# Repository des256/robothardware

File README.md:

# robothardware — Robot Backbone PCB

KiCad workspace for the backbone board described in [`HARDWARE.md`](HARDWARE.md)
(how and with what) and [`FUNCTIONAL.md`](FUNCTIONAL.md) (what it does, seen from
its connectors and from software).
Tooling follows [kevins-kicad-helpers](https://github.com/lynaghk/kevins-kicad-helpers)
(vendored at `vendor/kevins-kicad-helpers`, on PATH via `mise.toml`).

## Toolchain status

1. **mise** — installed at `~/.local/bin/mise`; activate in your shell
   (`eval "$(mise activate bash)"` in `~/.bashrc`, the installer appended it).
   Run `mise trust && mise install` once in this directory.
2. **sqlite3** — static binary at `~/.local/bin/sqlite3` (needed by the
   parts-database script; not in mise).
3. **KiCad 10** — installed (10.0.6; verify with `kicad-cli --version`).
4. **KiCad plugins** — installed: bennymeg/Fabrication-Toolkit (JLCPCB outputs;
   `kkh build` drives it) and CDFER/JLCPCB-Kicad-Library (symbols/footprints
   for JLC Basic parts).
5. **Analyzer toolchain** (`kkh check` / `kkh-analyze-schematic` run a JVM
   Clojure tool) — Java temurin-25 and clj-kondo via
   `mise -C vendor/kevins-kicad-helpers/analyzer install`. Clojure needs a
   workaround: mise 2026.8.14 cannot resolve the registry name `clojure`, so
   the CLI was installed through the asdf plugin the analyzer's `mise.lock`
   names (`mise plugins install clojure https://github.com/asdf-community/asdf-clojure.git`)
   and symlinked onto the PATH: `~/.local/bin/{clojure,clj}` →
   `~/.local/share/mise/installs/clojure/1.12.5.1654/bin/`. `mise exec` then
   finds it from the ambient PATH. Verified: `kkh-analyze-schematic` runs.
6. **`KICAD_PYTHON`** — set in `mise.toml` to `/usr/bin/python3` (the PATH
   `python3` is PlatformIO's venv and cannot import `pcbnew`).

## Project layout

- `backbone/` — the KiCad project (`backbone.kicad_pro`, root sheet plus one file
  per block, see below); kkh tools discover it by scanning for `*.kicad_pro`.
  `0_backbone.kicad_sym` / `0_backbone.pretty/` / `0_backbone.3dshapes/` are the
  project-local libraries written by `kkh-import-easyeda-parts` (registered in
  the project `sym-lib-table` / `fp-lib-table`; reopen the project in KiCad
  after an import so it picks them up). Library status is tracked in the
  Schematic plan section.
- `jlcpcb_parts.db` — local JLCPCB catalog mirror (gitignored; rebuild anytime
  with `kkh-download-jlcpcb-parts-database jlcpcb_parts.db`). Check freshness:
  `sqlite3 jlcpcb_parts.db "SELECT value FROM meta WHERE key='generated_at'"`.
- `parts-shortlist.md` — distilled candidate parts per block, queried from the DB.
- `datasheets/` — part datasheets for every curated pick plus vendor reference
  designs and the ROBOTIS servo circuits (`datasheets/README.md` is the index;
  `datasheets/fetch.sh` re-downloads from `manifest.tsv`).

## Schematic plan (mirrors HARDWARE.md sections 1 and 8)

The hierarchy lives in `backbone/`. The root sheet `backbone.kicad_sch` is the
block diagram of FUNCTIONAL.md §3 and holds only sheet symbols; every block is
its own file, and the two repeated blocks are one file instantiated several
times:

| Page | Sheet file | Instances | Contents | Golden reference |
|------|------------|-----------|----------|------------------|
| 2 | `input` | 1 | J1, fuse, LM74700 + FET, SMBJ24A, bulk; J2 19 V out with its fuse | LM74700 datasheet |
| 3 | `buck-12v-servo` | 1 | LM5145 → `+12V_SERVO`, shared bulk bank | LM5145 EVM / WEBENCH |
| 4 | `buck-5v-servo` | 1 | LM5145 → `+5V_SERVO` (own file: values differ, and D1 may delete it) | same |
| 5 | `buck-5v-usb` | 1 | TPS54560 → `+5V_USB`, TLV62569 → `+3V3` | TPS54560 EVM |
| 6 | `usbc-upstream` | 1 | J3, HD3SS3220 (UFP, GPIO mode), VBUS_DET, ESD | HD3SS3220 checklist + EVM |
| 7 | `usb-hub` | 1 | TUSB8041, crystal, 1V1 LDO, straps, USB_VBUS divider | TUSB8041 EVM |
| 8–10 | `usb-port` | 3: `usb-port-1..3` = hub DS1..DS3 | SY6280 + Rset, TPD4E05U06, USBLC6-2, USB-A 3.0 receptacle | hub EVM downstream port |
| 11 | `servo-uart` | 1 | CH344Q on hub DS4, TNOW pull-downs, RXD pull-ups | CH344 datasheet |
| 12–15 | `servo-port` | 4: `servo-port-0..3` = CH344 UART0..3 | SP3485EN + LVC2G241 front-end, mode jumper, ESD, both connectors, both e-fuses / bulk / TVS | ROBOTIS circuits |

Every sheet starts with a note (golden references, LCSC parts, rails, open
FUNCTIONAL.md decisions) and its hierarchical pins on wire stubs. Anything that
must differ between instances cannot live in a multi-instance sheet: KiCad
stores only reference and unit per instance; values, footprints and DNP are
shared.

Conventions (see HARDWARE.md section 8):

- Rails are global power symbols — `+19V_IN`, `+19V_JETSON`, `+12V_SERVO`,
  `+5V_SERVO`, `+5V_USB`, `+3V3`, `+1V1_HUB`, `VBUS`, `GND` — with the
  `PWR_FLAG` on the sheet that produces the rail. In KiCad 10 a power symbol's
  Value is its net name, so a `power:+5V` symbol with Value `+5V_SERVO` *is*
  the `+5V_SERVO` rail. `VBUS` is reserved for the upstream USB-C VBUS (the
  < 10 µF check); the switched port outputs are `VBUS_OUT`.
- Signals cross sheets through hierarchical pins; the labels on the root name
  the top-level nets (`US_*` upstream ↔ hub, `DSn_*` hub ↔ ports, `UARTn_*`
  uart ↔ servo ports). Inside a multi-instance sheet nets get paths such as
  `/servo-port-0/DATA` — the net-class patterns and DRC rules key on them.
- Annotate with "First free after sheet number × 100" so a designator names
  its sheet; the pre-placed power symbols already follow it (`#PWR0201` is on
  sheet 2). This will renumber FUNCTIONAL.md's J1–J14 — update that table once
  the connectors are placed.
- `max_mA`: `kkh-analyze-schematic` sums every `max_mA` in the design
  regardless of rail and asserts ≤ 300 mA (hardcoded in
  `vendor/kevins-kicad-helpers/analyzer/src/kicad_analyzer/core.clj`), so put
  it only on the +3V3 ICs. The rail budgets stay in FUNCTIONAL.md §4.
- `kkh check` fails any placed part (non-DNP, with a footprint) whose `LCSC`
  field is empty — CDFER-library and `kkh-import-easyeda-parts` symbols carry
  it, symbols taken from KiCad's own libraries (`Device:R`, …) need it filled
  in by hand.

### Library status (what `kkh-import-easyeda-parts` has pulled so far)

Imported into `0_backbone` from LCSC, with the EasyEDA footprint and 3D model
(non-interactive run, so no KiCad standard footprint was substituted — review
each footprint against the datasheet drawing, V4):
TUSB8041IRGCR, CH344Q, SN74LVC2G241DCU, LM5145RGYR, TPS54560DDAR,
TLV62569DBVR, TPS16630PWPR, TPS25961DRVR, SY6280AAC, HD3SS3220RNHR,
LM74700QDBVRQ1, TPD4E05U06DQAR, USBLC6-2SC6, B4B-EH-A, B3B-EH-A, XT30PW-M,
HC-ST-003-01-J (USB-A 3.0), TYPE-C 24P QT.

Served by the installed CDFER JLCPCB library instead (symbols already carry
the LCSC field; place them from `PCM_JLCPCB-…`): SP3485EN-L/TR, SMBJ24A,
SMBJ13A, SMBJ6.0A, SM712.

KiCad's own libraries also ship symbols for TUSB8041, CH344Q, TLV62569DBV,
LM74700, TPD4E05U06DQA and USBLC6-2SC6 — either is fine, but a symbol taken
from KiCad's library needs its `LCSC` field filled by hand.

Alternates, imported as well so a swap is a symbol change: RTS5411S-GR,
CYUSB3304-68LTXC, CH344L, SN74LVC1G126DBVR, SN74LVC1G125DBVR, LM5143RHAR,
TPS2553DBVR, S4B-EH, S3B-EH, DC-005-A200, TYPE-C 24P QCHT.

EasyEDA's API rate-limits bulk pulls (HTTP 403 after ~20 parts within a
minute); wait a few minutes and rerun the same command for the parts that
failed. Reruns skip parts the library already has.

### Schematic ↔ PCB correspondence

KiCad has no sheet-to-layer mapping; sheets are functional, layers are copper.
The links that do exist, and where each one is set up:

| Link | Where | State |
|------|-------|-------|
| Stackup | `backbone.kicad_pcb`: 4 copper layers, In1.Cu named `GND` (plane), In2.Cu named `PWR` | set; enter the JLC04161H-7628 thicknesses in Board Setup → Physical Stackup |
| Net classes | `backbone.kicad_pro`: `USB3_SS`, `USB2_HS`, `RS485`, `TTL_DATA`, `PWR_19V`, `PWR_SERVO`, `PWR_USB`, `SW_NODE` | defined; USB3_SS / USB2_HS width and gap **still to fill from the JLCPCB impedance calculator** (they inherit Default until then); power-class widths are starting values |
| Class of a signal net | directive label on its stub inside the sheet (a multi-instance sheet applies it to every instance) | placed on every USB pair |
| Class of a rail / per-port net | `netclass_patterns` in `backbone.kicad_pro`: `+12V_SERVO`, `/servo-port-*/A`, `/servo-port-*/B`, `/servo-port-*/DATA`, `/servo-port-*/VDD_*`, `/usb-port-*/VBUS_OUT`, `/buck-*/SW*`, `/buck-*/BOOT*` | set — use these net names when drawing |
| Layer geometry and keep-outs | `backbone.kicad_dru`: USB3_SS on F.Cu only and without vias, 1 mm zone clearance to the USB pairs, SW_NODE on outer layers and 3 mm from signal classes, PWR_SERVO copper barred from a rule area named `usb_section` (draw and name it in the PCB editor) | written; check it with Board Setup → Custom Rules → "Check rule syntax" — `kicad-cli pcb drc` silently ignores rule-file errors |
| Sheet → board region | PCB editor: "Generate Placement Rule Areas…" (one area per hierarchical sheet), then "Pack and Move Footprints" | use after the first Update PCB from Schematic |
| Sheet → component class | `sheet_component_classes` enabled in `backbone.kicad_pro`; rules can use `A.hasComponentClass(...)` | enabled |

Workflow while drawing sheets. ERC on the skeleton reports only "Label not
connected", "Unconnected wire endpoint" and "Pin not connected" — one per
interface pin or rail that has no part on it yet; they disappear as the sheets
fill up. `kkh check` therefore stops at ERC until then, and afterwards at the
DRC schematic-parity step until footprints are placed:

```sh
kicad-cli sch erc --exit-code-violations -o /dev/stdout backbone/backbone.kicad_sch
kkh-analyze-schematic backbone/backbone.kicad_sch     # max_mA total, VBUS < 10 uF
kkh-import-easyeda-parts C544686 C2988084 ...          # symbols/footprints per LCSC number
```

From layout onward: `kkh check`, then `kkh build` for the JLCPCB order
package. Put `${KKH_VERSION_DATE}` on the silkscreen (the first `kkh check`
adds the placeholder text variable to `backbone.kicad_pro`; commit it).

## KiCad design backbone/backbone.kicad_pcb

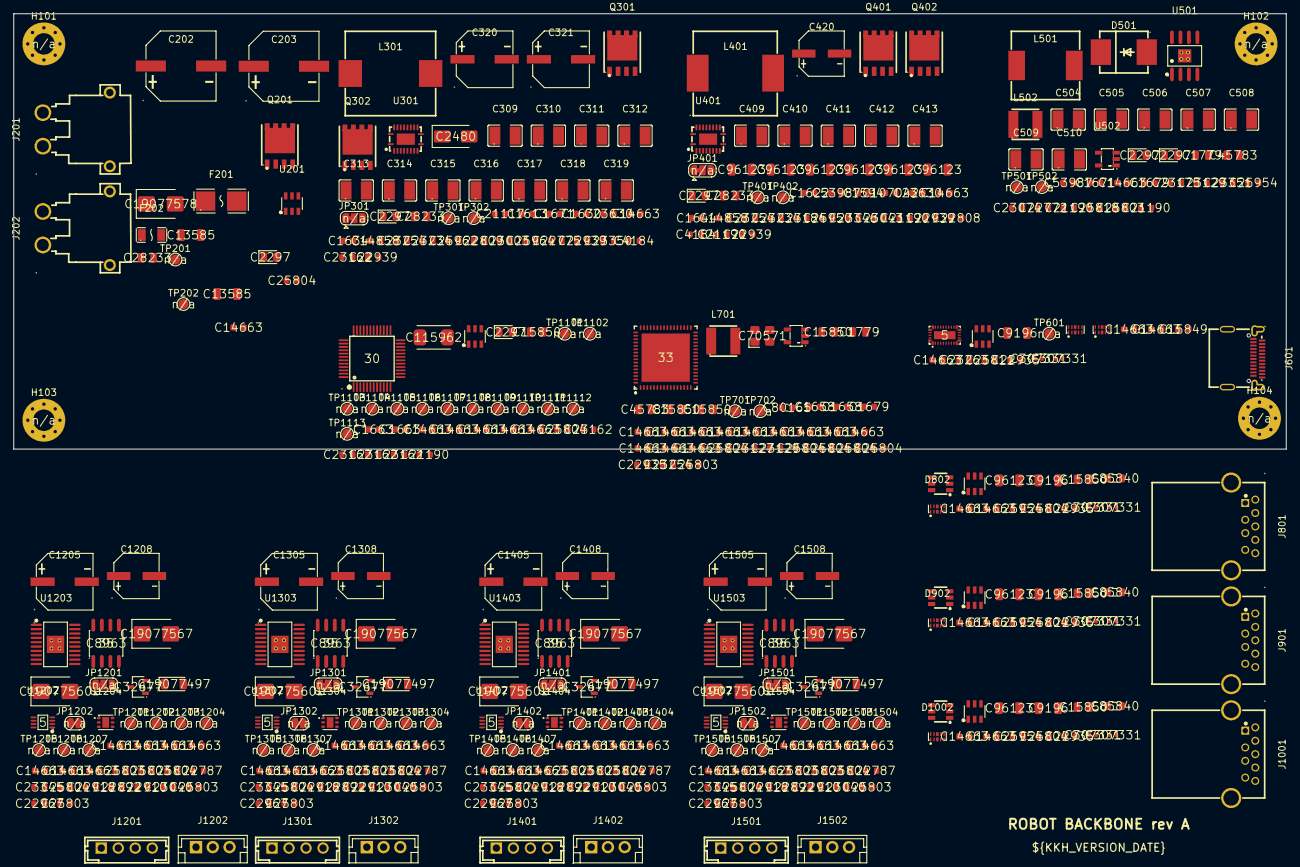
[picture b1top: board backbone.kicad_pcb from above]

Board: 4 copper layers, 190.0 x 65.0 mm, 430 parts (0 on the bottom side), 225 nets, no tracks yet.

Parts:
C201, C306, C406, C503, C603, C604, C606, C707, C708, C709, C710, C711, C712, C713, C714, C716, C717, C718, C719, C801, C804, C901, C904, C1001, C1004, C1103, C1104, C1105, C1106, C1107, C1201, C1202, C1203, C1204, C1206, C1207, C1209, C1301, C1302, C1303, C1304, C1306, C1307, C1309, C1401, C1402, C1403, C1404, C1406, C1407, C1409, C1501, C1502, C1503, C1504, C1506, C1507, C1509: 100nF; C_0603
C202, C203: 470uF 35V; CAP-SMD_BD10.0-L10.3-W10.3-LS11.3-FD
C204, C206: 10uF 50V; C_1206
C205, C307, C407: 100nF 100V; C_0805
C301: 33nF; C_0603
C302: 3.3nF; C_0603
C303, C502: 47pF; C_0603
C304: 680pF; C_0603
C305, C405: 2.2uF; C_0603
C308: 10pF; C_0603
C309, C310, C311, C312, C313: 4.7uF 100V; C1210
C314, C315, C316, C317, C508, C509, C510: 47uF 16V; C1210
C318, C319: 22uF 25V; C1210
C320, C321, C1205, C1305, C1405, C1505: 470uF 25V; CAP-SMD_BD8.0-L8.3-W8.3-LS9.0-FD_H10.5
C322, C421: 100pF; C_0603
C401: 47nF; C_0603
C402, C501: 4.7nF; C_0603
C403: 150pF; C_0603
C404: 1.8nF; C_0603
C408: 15pF; C_0603
C409, C410, C411, C412, C413, C504, C505, C506, C507: 2.2uF 100V; C1210
C414, C415, C416, C417, C418, C419, C803, C903, C1003: 47uF 10V; C_1206
C420, C1208, C1308, C1408, C1508: 470uF 10V; CAP-SMD_BD6.3-L6.6-W6.6-LS7.3-FD-H7.7
C511, C704: 6.8pF; C_0603
C512, C705: 4.7uF; C_0805
C513, C706: 22uF; C_0805
C601, C602, C805, C806, C905, C906, C1005, C1006: 100nF; C_0402
C605: 1uF; C_0603
C607, C807, C907, C1007: 1nF 2kV; C_1206
C701, C715, C720, C802, C902, C1002, C1108: 10uF; C_0805
C702, C703: 30pF; C_0603
C1101, C1102: 33pF; C_0603
D201: SMBJ24A; D_SMB
D202, D302, D401, D502, D503: LED Green; D_0805
D301: SS14; D_SMA
D501: B560C; SMC_L7.1-W6.2-LS8.1-RD
D601, D602, D802, D902, D1002: TPD4E05U06; USON-10_L2.5-W1.0-P0.50-BL
D603, D801, D901, D1001, D1102: USBLC6-2SC6; SOT-23-6_L2.9-W1.6-P0.95-LS2.8-BL
D1101: LED ACT; D_0805
D1201, D1301, D1401, D1501: PSM712-LF-T7; SOT-23-3_L3.0-W1.7-P0.95-LS2.9-BR
D1202, D1302, D1402, D1502: SMF5.0A; D_SOD-123FL
D1203, D1303, D1403, D1503: SMBJ13A; D_SMB
D1204, D1304, D1404, D1504: SMBJ6.0A; D_SMB
F201: 15A T 2410; FUSE-SMD_L6.1-W2.7
F202: 4A T 1206; F1206
FB701: BLM18PG221SN1D; FB_0603
FB801, FB901, FB1001: BLM21PG221SN1D; FB_0805
H101, H102, H103, H104: M3; MountingHole_3.2mm_M3_Pad_Via
J201, J202: XT30PW-M; CONN-TH_XT30PW-M
J601: USB-C 24P receptacle; USB-C-SMD_TYPE-C-24P-QT
J801, J901, J1001: USB-A 3.0 receptacle; USB-3.0-A-TH_HC-ST-003-01-Z
J1201, J1301, J1401, J1501: RS-485 JST EH 4p; CONN-TH_B4B-EH-A-LF-SN
J1202, J1302, J1402, J1502: TTL JST EH 3p; CONN-TH_B3B-EH-A-LF-SN
JP301, JP401: SYNCIN: 1-2 GND=DEM, 2-3 VCC=FPWM; SolderJumper-3_P1.3mm_Bridged12_RoundedPad1.0x1.5mm
JP1201, JP1301, JP1401, JP1501: MODE: 1-2 RS-485 (default), 2-3 TTL; SolderJumper-3_P1.3mm_Bridged12_RoundedPad1.0x1.5mm
JP1202, JP1302, JP1402, JP1502: MODE: bridged = auto-retry, open = latch-off; SolderJumper-2_P1.3mm_Bridged_RoundedPad1.0x1.5mm
L301: 4.7uH 20A; IND-SMD_L13.5-W12.6
L401: 3.3uH 18A; IND-SMD_L13.5-W12.6_125CDMCC-DS
L501: 7.2uH 6A; IND-SMD_L10.2-W10.2_7447798720
L502, L701: 2.2uH 3.4A; IND-SMD_L4.0-W4.0_LQH44PN2R2MP0L
Q201, Q301, Q302, Q401, Q402: CSD18532Q5B; SON-8_L5.0-W6.0-P1.27-BL-1
R201, R701, R704, R705, R706, R707, R802, R902, R1002, R1101, R1203, R1206, R1303, R1306, R1403, R1406, R1503, R1506: 10k; R_0603
R301, R401, R709: 82k; R_0603
R302, R402: 7.5k; R_0603
R303: 24.9k; R_0603
R304: 15k; R_0603
R305: 33.2k; R_0603
R306: 2.37k; R_0603
R307: 100; R_0603
R308, R312, R408, R412: 2.2; R_0603
R309: 240; R_0603
R310, R410: 20k; R_0603
R311, R1102, R1103, R1104, R1105: 4.7k; R_0603
R403: 49.9k; R_0603
R404: 11k; R_0603
R405: 23.2k; R_0603
R406: 4.42k; R_0603
R407, R411, R507, R510, R1106: 1k; R_0603
R409: 150; R_0603
R501: 442k; R_0603
R502, R703: 90.9k; R_0603
R503: 243k; R_0603
R504, R801, R901, R1001: 16.9k; R_0603
R505: 53.6k; R_0603
R506: 10.2k; R_0603
R508: 453k; R_0603
R509, R710, R1201, R1202, R1211, R1213, R1301, R1302, R1311, R1313, R1401, R1402, R1411, R1413, R1501, R1502, R1511, R1513: 100k; R_0603
R601: 910k; R_0603
R602: 200k; R_0603
R603, R708, R803, R903, R1003: 1M; R_0603
R702: 9.53k; R_0603
R1204, R1304, R1404, R1504: 120; R_0603
R1205, R1305, R1405, R1505: 22; R_0603
R1207, R1307, R1407, R1507: 249k; R_0603
R1208, R1308, R1408, R1508: 18.2k; R_0603
R1209, R1309, R1409, R1509: 20.5k; R_0603
R1210, R1310, R1410, R1510: 4.02k; R_0603
R1212, R1312, R1412, R1512: 27k; R_0603
TP201: +19V_IN; TestPoint_Pad_D1.5mm
TP202: +19V_JETSON; TestPoint_Pad_D1.5mm
TP301, TP401: PGOOD; TestPoint_Pad_D1.5mm
TP302: +12V_SERVO; TestPoint_Pad_D1.5mm
TP402: +5V_SERVO; TestPoint_Pad_D1.5mm
TP501: +5V_USB; TestPoint_Pad_D1.5mm
TP502: +3V3; TestPoint_Pad_D1.5mm
TP601: DIR; TestPoint_Pad_D1.5mm
TP701: GRSTz; TestPoint_Pad_D1.5mm
TP702: VDD_HUB; TestPoint_Pad_D1.5mm
TP1101: RESET; TestPoint_Pad_D1.5mm
TP1102: UART0_TXD; TestPoint_Pad_D1.5mm
TP1103: UART0_RXD; TestPoint_Pad_D1.5mm
TP1104: UART0_TNOW; TestPoint_Pad_D1.5mm
TP1105: UART1_TXD; TestPoint_Pad_D1.5mm
TP1106: UART1_RXD; TestPoint_Pad_D1.5mm
TP1107: UART1_TNOW; TestPoint_Pad_D1.5mm
TP1108: UART2_TXD; TestPoint_Pad_D1.5mm
TP1109: UART2_RXD; TestPoint_Pad_D1.5mm
TP1110: UART2_TNOW; TestPoint_Pad_D1.5mm
TP1111: UART3_TXD; TestPoint_Pad_D1.5mm
TP1112: UART3_RXD; TestPoint_Pad_D1.5mm
TP1113: UART3_TNOW; TestPoint_Pad_D1.5mm
TP1201, TP1301, TP1401, TP1501: SHDN_485; TestPoint_Pad_D1.5mm
TP1202, TP1302, TP1402, TP1502: TXD; TestPoint_Pad_D1.5mm
TP1203, TP1303, TP1403, TP1503: RXD; TestPoint_Pad_D1.5mm
TP1204, TP1304, TP1404, TP1504: TNOW; TestPoint_Pad_D1.5mm
TP1205, TP1305, TP1405, TP1505: A; TestPoint_Pad_D1.5mm
TP1206, TP1306, TP1406, TP1506: B; TestPoint_Pad_D1.5mm
TP1207, TP1307, TP1407, TP1507: DATA; TestPoint_Pad_D1.5mm
U201: LM74700QDBVRQ1; SOT-23-6_L2.9-W1.6-P0.95-LS2.8-BL
U301, U401: LM5145RGYR; VQFN-20_L4.5-W3.5-P0.50-BL-EP
U501: TPS54560DDAR; SOIC-8_L5.0-W4.0-P1.27-LS6.0-BL-EP2.0
U502, U702: TLV62569DBVR; SOT-23-5_L3.0-W1.7-P0.95-LS2.8-BR
U601: HD3SS3220RNHR; WQFN-30_L4.5-W2.5-P0.4-BL-EP
U701: TUSB8041IRGCR; QFN-64_L9.0-W9.0-P0.50-BL-EP7.2
U801, U901, U1001: TPS2553DBVR; SOT-23-6_L2.9-W1.6-P0.95-LS2.8-BR
U1101: CH344Q; LQFP-48_L7.0-W7.0-P0.50-LS9.0-BL
U1201, U1301, U1401, U1501: SP3485EN-L/TR; SOIC-8_L5.0-W4.0-P1.27-LS6.0-BL
U1202, U1302, U1402, U1502: SN74LVC2G241DCU; VSSOP-8_L2.3-W2.0-P0.50-LS3.1-BR
U1203, U1303, U1403, U1503: TPS16630PWPR; HTSSOP-20_L6.5-W4.4-P0.65-LS6.4-TL-EP2.58
U1204, U1304, U1404, U1504: TPS25961DRVR; WSON-6_L2.0-W2.0-P0.65-TL-EP
Y701: 24MHz 18pF; OSC-SMD_4P-L3.2-W2.5-BL
Y1101: 8MHz 20pF; CRYSTAL-SMD_L5.0-W3.2

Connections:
+1V1_HUB: C704.1, C706.1, FB701.1, L701.2, R709.1
+3V3: C511.1, C513.1, C603.1, C604.1, C716.1, C717.1, C718.1, C719.1, C720.1, C1104.1, C1105.1, C1106.1, C1107.1, C1108.1, C1201.1, C1202.1, C1301.1, C1302.1, C1401.1, C1402.1, C1501.1, C1502.1, D1102.5, L502.2, R508.1, R510.1, R602.1, R701.1, R705.1, R706.1, R707.1, R802.1, R902.1, R1002.1, R1101.1, R1106.1, R1201.1, R1202.1, R1203.1, R1206.1, R1301.1, R1302.1, R1303.1, R1306.1, R1401.1, R1402.1, R1403.1, R1406.1, R1501.1, R1502.1, R1503.1, R1506.1, TP502.1, U601.8, U701.16, U701.34, U701.52, U701.63, U1101.9, U1101.24, U1101.36, U1101.48, U1201.8, U1202.8, U1301.8, U1302.8, U1401.8, U1402.8, U1501.8, U1502.8
+5V_SERVO: C414.1, C415.1, C416.1, C417.1, C418.1, C419.1, C420.1, C1207.1, C1307.1, C1407.1, C1507.1, L401.2, R405.1, R407.1, R411.1, R1213.1, R1313.1, R1413.1, R1513.1, TP402.1, U1204.6, U1304.6, U1404.6, U1504.6
+5V_USB: C508.1, C509.1, C510.1, C512.1, C605.1, C606.1, C705.1, C801.1, C802.1, C901.1, C902.1, C1001.1, C1002.1, L501.2, R505.1, R507.1, TP501.1, U502.1, U502.4, U601.30, U702.1, U702.4, U801.1, U901.1, U1001.1
+12V_SERVO: C314.1, C315.1, C316.1, C317.1, C318.1, C319.1, C320.1, C321.1, C1204.1, C1304.1, C1404.1, C1504.1, D301.2, L301.2, R305.1, R307.1, R311.1, R1207.1, R1211.1, R1307.1, R1311.1, R1407.1, R1411.1, R1507.1, R1511.1, TP302.1, U1203.1, U1203.2, U1203.3, U1203.6, U1303.1, U1303.2, U1303.3, U1303.6, U1403.1, U1403.2, U1403.3, U1403.6, U1503.1, U1503.2, U1503.3, U1503.6
+19V_IN: C202.1, C203.1, C204.1, C205.1, C307.1, C309.1, C310.1, C311.1, C312.1, C313.1, C407.1, C409.1, C410.1, C411.1, C412.1, C413.1, C504.1, C505.1, C506.1, C507.1, F202.1, Q201.5, Q201.6, Q201.7, Q201.8, Q201.9, Q301.5, Q301.6, Q301.7, Q301.8, Q301.9, Q401.5, Q401.6, Q401.7, Q401.8, Q401.9, R201.1, R301.1, R401.1, R501.1, TP201.1, U201.4, U301.20, U401.20, U501.2
+19V_JETSON: C206.1, F202.2, J202.2, TP202.1
/DS1_DM: D801.4, U701.2
/DS1_DP: D801.6, U701.1
/DS1_OVERCUR_N: R705.2, R802.2, U701.46, U801.4
/DS1_PWRCTL: U701.36, U801.3
/DS1_SSRX_N: D802.5, J801.5, U701.7
/DS1_SSRX_P: D802.4, J801.6, U701.6
/DS1_SSTX_N: C806.1, U701.4
/DS1_SSTX_P: C805.1, U701.3
/DS2_DM: D901.4, U701.10
/DS2_DP: D901.6, U701.9
/DS2_OVERCUR_N: R706.2, R902.2, U701.47, U901.4
/DS2_PWRCTL: U701.35, U901.3
/DS2_SSRX_N: D902.5, J901.5, U701.15
/DS2_SSRX_P: D902.4, J901.6, U701.14
/DS2_SSTX_N: C906.1, U701.12
/DS2_SSTX_P: C905.1, U701.11
/DS3_DM: D1001.4, U701.18
/DS3_DP: D1001.6, U701.17
/DS3_OVERCUR_N: R707.2, R1002.2, U701.44, U1001.4
/DS3_PWRCTL: U701.33, U1001.3
/DS3_SSRX_N: D1002.5, J1001.5, U701.23
/DS3_SSRX_P: D1002.4, J1001.6, U701.22
/DS3_SSTX_N: C1006.1, U701.20
/DS3_SSTX_P: C1005.1, U701.19
/DS4_DM: D1102.4, U701.25
/DS4_DP: D1102.6, U701.24
/UART0_RXD: R1203.2, TP1103.1, TP1203.1, U1101.31, U1201.1, U1202.6
/UART0_TNOW: JP1201.2, R1102.1, TP1104.1, TP1204.1, U1101.39, U1201.3, U1202.7
/UART0_TXD: TP1102.1, TP1202.1, U1101.30, U1201.4, U1202.5
/UART1_RXD: R1303.2, TP1106.1, TP1303.1, U1101.13, U1301.1, U1302.6
/UART1_TNOW: JP1301.2, R1103.1, TP1107.1, TP1304.1, U1101.18, U1301.3, U1302.7
/UART1_TXD: TP1105.1, TP1302.1, U1101.12, U1301.4, U1302.5
/UART2_RXD: R1403.2, TP1109.1, TP1403.1, U1101.22, U1401.1, U1402.6
/UART2_TNOW: JP1401.2, R1104.1, TP1110.1, TP1404.1, U1101.19, U1401.3, U1402.7
/UART2_TXD: TP1108.1, TP1402.1, U1101.21, U1401.4, U1402.5
/UART3_RXD: R1503.2, TP1112.1, TP1503.1, U1101.38, U1501.1, U1502.6
/UART3_TNOW: JP1501.2, R1105.1, TP1113.1, TP1504.1, U1101.34, U1501.3, U1502.7
/UART3_TXD: TP1111.1, TP1502.1, U1101.37, U1501.4, U1502.5
/US_DM: D603.4, U701.54
/US_DP: D603.6, U701.53
/US_SSRX_N: U601.10, U701.59
/US_SSRX_P: U601.9, U701.58
/US_SSTX_N: C602.1, U701.56
/US_SSTX_P: C601.1, U701.55
/buck-5v-servo/BOOT: R408.1, U401.17
/buck-5v-servo/COMP: C403.1, R404.1, U401.4
/buck-5v-servo/FB: C402.2, C403.2, C404.2, R405.2, R406.1, U401.5
/buck-5v-servo/HO: Q401.4, U401.18
/buck-5v-servo/ILIM: C408.1, R409.1, U401.11
/buck-5v-servo/LO: Q402.4, U401.13
/buck-5v-servo/PGOOD: R410.2, TP401.1, U401.10
/buck-5v-servo/RT: R403.1, U401.2
/buck-5v-servo/SS: C401.1, U401.3
/buck-5v-servo/SW: C406.2, L401.1, Q401.1, Q401.2, Q401.3, Q402.5, Q402.6, Q402.7, Q402.8, Q402.9, R409.2, R412.1, U401.19
/buck-5v-servo/SYNCIN: JP401.2, U401.8
/buck-5v-servo/UVLO: R401.2, R402.1, U401.1
/buck-5v-servo/VCC: C405.1, JP401.3, R410.1, U401.14
/buck-5v-usb/BOOT: C503.1, U501.1
/buck-5v-usb/COMP: C502.1, R504.1, U501.6
/buck-5v-usb/EN: R501.2, R502.1, U501.3
/buck-5v-usb/FB: R505.2, R506.1, U501.5
/buck-5v-usb/FB_3V3: C511.2, R508.2, R509.1, U502.5
/buck-5v-usb/RT: R503.1, U501.4
/buck-5v-usb/SW: C503.2, D501.1, L501.1, U501.8
/buck-5v-usb/SW_3V3: L502.1, U502.3
/buck-12v-servo/BOOT: R308.1, U301.17
/buck-12v-servo/COMP: C303.1, R304.1, U301.4
/buck-12v-servo/FB: C302.2, C303.2, C304.2, R305.2, R306.1, U301.5
/buck-12v-servo/HO: Q301.4, U301.18
/buck-12v-servo/ILIM: C308.1, R309.1, U301.11
/buck-12v-servo/LO: Q302.4, U301.13
/buck-12v-servo/PGOOD: R310.2, TP301.1, U301.10
/buck-12v-servo/RT: R303.1, U301.2
/buck-12v-servo/SS: C301.1, U301.3
/buck-12v-servo/SW: C306.2, L301.1, Q301.1, Q301.2, Q301.3, Q302.5, Q302.6, Q302.7, Q302.8, Q302.9, R309.2, R312.1, U301.19
/buck-12v-servo/SYNCIN: JP301.2, U301.8
/buck-12v-servo/UVLO: R301.2, R302.1, U301.1
/buck-12v-servo/VCC: C305.1, D301.1, JP301.3, R310.1, U301.14
/input/GATE: Q201.4, U201.5
/input/VCAP: C201.1, U201.1
/input/VIN_F: C201.2, D201.1, F201.2, Q201.1, Q201.2, Q201.3, U201.3, U201.6
/input/VIN_RAW: F201.1, J201.2
/servo-port-0/A: D1201.1, J1201.3, R1204.1, TP1205.1, U1201.6
/servo-port-0/B: D1201.2, J1201.4, R1204.2, TP1206.1, U1201.7
/servo-port-0/DATA: D1202.1, J1202.3, R1205.2, R1206.2, TP1207.1
/servo-port-0/DATA_BUF: R1205.1, U1202.2, U1202.3
/servo-port-0/DVDT_485: C1203.1, U1203.10
/servo-port-0/EN_TTL: R1213.2, U1204.5
/servo-port-0/ILIM_485: R1210.1, U1203.11
/servo-port-0/ILIM_TTL: R1212.1, U1204.3
/servo-port-0/MODE_485: JP1202.1, U1203.12
/servo-port-0/OE_TTL: JP1201.3, R1202.2, U1202.1
/servo-port-0/OVP_485: R1207.2, R1208.1, U1203.8
/servo-port-0/RE_485: JP1201.1, R1201.2, U1201.2
/servo-port-0/SHDN_485: R1211.2, TP1201.1, U1203.13
/servo-port-0/UVLO_485: R1208.2, R1209.1, U1203.7
/servo-port-0/VDD_485: C1205.1, C1206.1, D1203.1, J1201.2, U1203.18, U1203.19, U1203.20
/servo-port-0/VDD_TTL: C1208.1, C1209.1, D1204.1, J1202.2, U1204.1
/servo-port-1/A: D1301.1, J1301.3, R1304.1, TP1305.1, U1301.6
/servo-port-1/B: D1301.2, J1301.4, R1304.2, TP1306.1, U1301.7
/servo-port-1/DATA: D1302.1, J1302.3, R1305.2, R1306.2, TP1307.1
/servo-port-1/DATA_BUF: R1305.1, U1302.2, U1302.3
/servo-port-1/DVDT_485: C1303.1, U1303.10
/servo-port-1/EN_TTL: R1313.2, U1304.5
/servo-port-1/ILIM_485: R1310.1, U1303.11
/servo-port-1/ILIM_TTL: R1312.1, U1304.3
/servo-port-1/MODE_485: JP1302.1, U1303.12
/servo-port-1/OE_TTL: JP1301.3, R1302.2, U1302.1
/servo-port-1/OVP_485: R1307.2, R1308.1, U1303.8
/servo-port-1/RE_485: JP1301.1, R1301.2, U1301.2
/servo-port-1/SHDN_485: R1311.2, TP1301.1, U1303.13
/servo-port-1/UVLO_485: R1308.2, R1309.1, U1303.7
/servo-port-1/VDD_485: C1305.1, C1306.1, D1303.1, J1301.2, U1303.18, U1303.19, U1303.20
/servo-port-1/VDD_TTL: C1308.1, C1309.1, D1304.1, J1302.2, U1304.1
/servo-port-2/A: D1401.1, J1401.3, R1404.1, TP1405.1, U1401.6
/servo-port-2/B: D1401.2, J1401.4, R1404.2, TP1406.1, U1401.7
/servo-port-2/DATA: D1402.1, J1402.3, R1405.2, R1406.2, TP1407.1
/servo-port-2/DATA_BUF: R1405.1, U1402.2, U1402.3
/servo-port-2/DVDT_485: C1403.1, U1403.10
/servo-port-2/EN_TTL: R1413.2, U1404.5
/servo-port-2/ILIM_485: R1410.1, U1403.11
/servo-port-2/ILIM_TTL: R1412.1, U1404.3
/servo-port-2/MODE_485: JP1402.1, U1403.12
/servo-port-2/OE_TTL: JP1401.3, R1402.2, U1402.1
/servo-port-2/OVP_485: R1407.2, R1408.1, U1403.8
/servo-port-2/RE_485: JP1401.1, R1401.2, U1401.2
/servo-port-2/SHDN_485: R1411.2, TP1401.1, U1403.13
/servo-port-2/UVLO_485: R1408.2, R1409.1, U1403.7
/servo-port-2/VDD_485: C1405.1, C1406.1, D1403.1, J1401.2, U1403.18, U1403.19, U1403.20
/servo-port-2/VDD_TTL: C1408.1, C1409.1, D1404.1, J1402.2, U1404.1
/servo-port-3/A: D1501.1, J1501.3, R1504.1, TP1505.1, U1501.6
/servo-port-3/B: D1501.2, J1501.4, R1504.2, TP1506.1, U1501.7
/servo-port-3/DATA: D1502.1, J1502.3, R1505.2, R1506.2, TP1507.1
/servo-port-3/DATA_BUF: R1505.1, U1502.2, U1502.3
/servo-port-3/DVDT_485: C1503.1, U1503.10
/servo-port-3/EN_TTL: R1513.2, U1504.5
/servo-port-3/ILIM_485: R1510.1, U1503.11
/servo-port-3/ILIM_TTL: R1512.1, U1504.3
/servo-port-3/MODE_485: JP1502.1, U1503.12
/servo-port-3/OE_TTL: JP1501.3, R1502.2, U1502.1
/servo-port-3/OVP_485: R1507.2, R1508.1, U1503.8
/servo-port-3/RE_485: JP1501.1, R1501.2, U1501.2
/servo-port-3/SHDN_485: R1511.2, TP1501.1, U1503.13
/servo-port-3/UVLO_485: R1508.2, R1509.1, U1503.7
/servo-port-3/VDD_485: C1505.1, C1506.1, D1503.1, J1501.2, U1503.18, U1503.19, U1503.20
/servo-port-3/VDD_TTL: C1508.1, C1509.1, D1504.1, J1502.2, U1504.1
/servo-uart/ACT: D1101.1, U1101.14
/servo-uart/RESET: C1103.1, R1101.2, TP1101.1, U1101.7
/servo-uart/UDM: D1102.3, U1101.42
/servo-uart/UDP: D1102.1, U1101.43
/servo-uart/XI: C1101.1, U1101.5, Y1101.1
/servo-uart/XO: C1102.1, U1101.6, Y1101.2
/usb-hub/FB_1V1: C704.2, R709.2, R710.1, U702.5
/usb-hub/GRSTz: C701.1, R701.2, TP701.1, U701.50
/usb-hub/SW_1V1: L701.1, U702.3
/usb-hub/USB_R1: R702.1, U701.64
/usb-hub/USB_VBUS: R703.2, R704.1, U701.48
/usb-hub/VDD_HUB: C707.1, C708.1, C709.1, C710.1, C711.1, C712.1, C713.1, C714.1, C715.1, FB701.2, TP702.1, U701.5, U701.8, U701.13, U701.21, U701.28, U701.31, U701.51, U701.57
/usb-hub/XI: C702.1, R708.1, U701.62, Y701.1
/usb-hub/XO: C703.1, R708.2, U701.61, Y701.3
/usb-port-1/DM_J: D801.3, J801.2
/usb-port-1/DP_J: D801.1, J801.3
/usb-port-1/ILIM: R801.1, U801.5
/usb-port-1/SHIELD: C807.1, J801.10, J801.11, R803.1
/usb-port-1/SSTX_N_J: C806.2, D802.2, J801.8
/usb-port-1/SSTX_P_J: C805.2, D802.1, J801.9
/usb-port-1/VBUS_J: C804.1, D801.5, FB801.2, J801.1
/usb-port-1/VBUS_OUT: C803.1, FB801.1, U801.6
/usb-port-2/DM_J: D901.3, J901.2
/usb-port-2/DP_J: D901.1, J901.3
/usb-port-2/ILIM: R901.1, U901.5
/usb-port-2/SHIELD: C907.1, J901.10, J901.11, R903.1
/usb-port-2/SSTX_N_J: C906.2, D902.2, J901.8
/usb-port-2/SSTX_P_J: C905.2, D902.1, J901.9
/usb-port-2/VBUS_J: C904.1, D901.5, FB901.2, J901.1
/usb-port-2/VBUS_OUT: C903.1, FB901.1, U901.6
/usb-port-3/DM_J: D1001.3, J1001.2
/usb-port-3/DP_J: D1001.1, J1001.3
/usb-port-3/ILIM: R1001.1, U1001.5
/usb-port-3/SHIELD: C1007.1, J1001.10, J1001.11, R1003.1
/usb-port-3/SSTX_N_J: C1006.2, D1002.2, J1001.8
/usb-port-3/SSTX_P_J: C1005.2, D1002.1, J1001.9
/usb-port-3/VBUS_J: C1004.1, D1001.5, FB1001.2, J1001.1
/usb-port-3/VBUS_OUT: C1003.1, FB1001.1, U1001.6
/usbc-upstream/CC1: J601.A5, U601.2
/usbc-upstream/CC2: J601.B5, U601.1
/usbc-upstream/C_RX1N: D601.5, J601.B10, U601.14
/usbc-upstream/C_RX1P: D601.4, J601.B11, U601.15
/usbc-upstream/C_RX2N: D602.5, J601.A10, U601.18
/usbc-upstream/C_RX2P: D602.4, J601.A11, U601.19
/usbc-upstream/C_TX1N: D601.2, J601.A3, U601.16
/usbc-upstream/C_TX1P: D601.1, J601.A2, U601.17
/usbc-upstream/C_TX2N: D602.2, J601.B3, U601.20
/usbc-upstream/C_TX2P: D602.1, J601.B2, U601.21
/usbc-upstream/DIR: R602.2, TP601.1, U601.11
/usbc-upstream/DM_C: D603.3, J601.A7, J601.B7
/usbc-upstream/DP_C: D603.1, J601.A6, J601.B6
/usbc-upstream/SHIELD_C: C607.1, J601.3, J601.4, J601.25, R603.1
/usbc-upstream/SSTX_N_C: C602.2, U601.7
/usbc-upstream/SSTX_P_C: C601.2, U601.6
/usbc-upstream/VBUS_DET: R601.2, U601.5
GND: C202.2, C203.2, C204.2, C205.2, C206.2, C301.2, C305.2, C307.2, C308.2, C309.2, C310.2, C311.2, C312.2, C313.2, C314.2, C315.2, C316.2, C317.2, C318.2, C319.2, C320.2, C321.2, C322.2, C401.2, C405.2, C407.2, C408.2, C409.2, C410.2, C411.2, C412.2, C413.2, C414.2, C415.2, C416.2, C417.2, C418.2, C419.2, C420.2, C421.2, C501.2, C502.2, C504.2, C505.2, C506.2, C507.2, C508.2, C509.2, C510.2, C512.2, C513.2, C603.2, C604.2, C605.2, C606.2, C607.2, C701.2, C702.2, C703.2, C705.2, C706.2, C707.2, C708.2, C709.2, C710.2, C711.2, C712.2, C713.2, C714.2, C715.2, C716.2, C717.2, C718.2, C719.2, C720.2, C801.2, C802.2, C803.2, C804.2, C807.2, C901.2, C902.2, C903.2, C904.2, C907.2, C1001.2, C1002.2, C1003.2, C1004.2, C1007.2, C1101.2, C1102.2, C1103.2, C1104.2, C1105.2, C1106.2, C1107.2, C1108.2, C1201.2, C1202.2, C1203.2, C1204.2, C1205.2, C1206.2, C1207.2, C1208.2, C1209.2, C1301.2, C1302.2, C1303.2, C1304.2, C1305.2, C1306.2, C1307.2, C1308.2, C1309.2, C1401.2, C1402.2, C1403.2, C1404.2, C1405.2, C1406.2, C1407.2, C1408.2, C1409.2, C1501.2, C1502.2, C1503.2, C1504.2, C1505.2, C1506.2, C1507.2, C1508.2, C1509.2, D201.2, D202.1, D302.1, D401.1, D501.2, D502.1, D503.1, D601.3, D601.8, D602.3, D602.8, D603.2, D801.2, D802.3, D802.8, D901.2, D902.3, D902.8, D1001.2, D1002.3, D1002.8, D1102.2, D1201.3, D1202.2, D1203.2, D1204.2, D1301.3, D1302.2, D1303.2, D1304.2, D1401.3, D1402.2, D1403.2, D1404.2, D1501.3, D1502.2, D1503.2, D1504.2, J201.1, J201.3, J201.4, J202.1, J202.3, J202.4, J601.A1, J601.A12, J601.B1, J601.B12, J801.4, J801.7, J901.4, J901.7, J1001.4, J1001.7, J1201.1, J1202.1, J1301.1, J1302.1, J1401.1, J1402.1, J1501.1, J1502.1, JP301.1, JP401.1, JP1202.2, JP1302.2, JP1402.2, JP1502.2, Q302.1, Q302.2, Q302.3, Q402.1, Q402.2, Q402.3, R302.2, R303.2, R306.2, R402.2, R403.2, R406.2, R502.2, R503.2, R506.2, R509.2, R603.2, R702.2, R704.2, R710.2, R801.2, R803.2, R901.2, R903.2, R1001.2, R1003.2, R1102.2, R1103.2, R1104.2, R1105.2, R1209.2, R1210.2, R1212.2, R1309.2, R1310.2, R1312.2, R1409.2, R1410.2, R1412.2, R1509.2, R1510.2, R1512.2, U201.2, U301.6, U301.12, U301.15, U301.21, U401.6, U401.12, U401.15, U401.21, U501.7, U501.9, U502.2, U601.3, U601.4, U601.12, U601.13, U601.28, U601.29, U601.31, U701.49, U701.65, U702.2, U801.2, U901.2, U1001.2, U1101.8, U1101.20, U1101.23, U1101.35, U1101.44, U1101.47, U1201.5, U1202.4, U1203.9, U1203.21, U1204.2, U1204.4, U1204.7, U1301.5, U1302.4, U1303.9, U1303.21, U1304.2, U1304.4, U1304.7, U1401.5, U1402.4, U1403.9, U1403.21, U1404.2, U1404.4, U1404.7, U1501.5, U1502.4, U1503.9, U1503.21, U1504.2, U1504.4, U1504.7, Y701.2, Y701.4
unnamed: C302.1, R304.2
unnamed: C304.1, R307.2
unnamed: C306.1, R308.2
unnamed: C322.1, R312.2
unnamed: C402.1, R404.2
unnamed: C404.1, R407.2
unnamed: C406.1, R408.2
unnamed: C421.1, R412.2
unnamed: C501.1, R504.2
unnamed: D202.2, R201.2
unnamed: D302.2, R311.2
unnamed: D401.2, R411.2
unnamed: D502.2, R507.2
unnamed: D503.2, R510.2
unnamed: D1101.2, R1106.2
VBUS: D603.5, J601.A4, J601.A9, J601.B4, J601.B9, R601.1, R703.1

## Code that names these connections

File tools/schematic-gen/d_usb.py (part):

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    s.label(u.pin('CC1'), 'CC1')
    s.power(u.pin('CURRENT_MODE'), 'GND')
    s.power(u.pin('PORT'), 'GND')
    s.label(u.pin('VBUS_DET'), 'VBUS_DET')
    s.label(u.pin('TXp'), 'SSTX_P_C')
    s.label(u.pin('TXn'), 'SSTX_N_C')
    s.power(u.pin('VCC33'), '+3V3')
    s.label(u.pin('RXp'), 'US_SSRX_P')
    s.label(u.pin('RXn'), 'US_SSRX_N')
    s.label(u.pin('DIR'), 'DIR')
    s.power(u.pin('ENn_MUX'), 'GND')
    for p in u.pins_named('GND'):
        s.power(p, 'GND')
    s.power(u.pin('EP'), 'GND')
    s.label(u.pin('RX1n'), 'C_RX1N')
    s.label(u.pin('RX1p'), 'C_RX1P')
    s.label(u.pin('TX1n'), 'C_TX1N')
    s.label(u.pin('TX1p'), 'C_TX1P')
    s.label(u.pin('RX2n'), 'C_RX2N')
    s.label(u.pin('RX2p'), 'C_RX2P')
    s.label(u.pin('TX2n'), 'C_TX2N')
    s.label(u.pin('TX2p'), 'C_TX2P')
    s.nc(u.pin('ADDR'), u.pin('INT_N/OUT3'), u.pin('VCONN_FAULT_N'), u.pin('SDA/OUT1'), u.pin('SCL/OUT2'), u.pin('ID'))
    s.power(u.pin('ENn_CC'), 'GND')
    s.power(u.pin('VDD5'), '+5V_USB')
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        for p in d.pins_named('GND'):
            s.power(p, 'GND')
    d3 = s.place('USBLC6-2SC6_C2687116', 'D', 254.0, 127, 0, value='USBLC6-2SC6', refnum=3)
    s.label(d3.pin('1'), 'DP_C')
    s.label(d3.pin('6'), 'US_DP')
    s.label(d3.pin('3'), 'DM_C')
    s.label(d3.pin('4'), 'US_DM')
    s.power(d3.pin('5'), 'VBUS')
    s.power(d3.pin('2'), 'GND')
    # receptacle
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        elif p.name == 'TEST':
            s.power(p, 'GND')
        elif p.name == 'GRSTz':
            s.label(p, 'GRSTz')
        elif p.name == 'USB_R1':
            s.label(p, 'USB_R1')
        elif p.name == 'USB_VBUS':
            s.label(p, 'USB_VBUS')
        elif p.name in ('XI', 'XO'):
            s.label(p, p.name)
        elif p.name == 'VDD':
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    u2 = s.place('TLV62569DBVR', 'U', 342.9, 86.36, 0, refnum=2)
    s.power(u2.pin('EN'), '+5V_USB')
    s.power(u2.pin('GND'), 'GND')
    s.label(u2.pin('SW'), 'SW_1V1')
    s.power(u2.pin('VIN'), '+5V_USB')
    s.label(u2.pin('FB'), 'FB_1V1')
    L2 = s.place('SMNR4020-2.2UH', 'L', 375.92, 99.06, 0, value='2.2uH 3.4A', refnum=1)
    s.label(L2.pin('1'), 'SW_1V1')
    s.power(L2.pin('2'), '+1V1_HUB')
    vR(s, 332.74, 121.92, '82k', 'pwr:+1V1_HUB', 'net:FB_1V1')
    vC(s, 345.44, 121.92, '6.8pF', 'pwr:+1V1_HUB', 'net:FB_1V1')
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    s.power(u.pin('IN'), '+5V_USB')
    s.power(u.pin('GND'), 'GND')
    s.label(u.pin('EN'), 'PWRCTL')
    s.label(u.pin('OUT'), 'VBUS_OUT')
    s.label(u.pin('ILIM'), 'ILIM')
    s.label(u.pin('/FAULT'), 'OVERCUR_N')
    vR(s, 139.7, 127, '16.9k', 'net:ILIM', 'pwr:GND')
    vR(s, 154.94, 127, '10k', 'pwr:+3V3', 'net:OVERCUR_N')
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    hC(s, 101.6, 167.64, '100nF', 'net:SSTX_P', 'net:SSTX_P_J', size='0402')
    hC(s, 101.6, 175.26, '100nF', 'net:SSTX_N', 'net:SSTX_N_J', size='0402')
    d2 = s.place('TPD4E05U06DQAR_C138714', 'D', 147.32, 172.72, 0, value='TPD4E05U06', refnum=2)
    s.label(d2.pin('D1+'), 'SSTX_P_J')
    s.label(d2.pin('D1-'), 'SSTX_N_J')
    s.label(d2.pin('D2+'), 'SSRX_P')
    s.label(d2.pin('D2-'), 'SSRX_N')
    for p in d2.pins_named('GND'):
        s.power(p, 'GND')
    d1 = s.place('USBLC6-2SC6_C2687116', 'D', 147.32, 203.2, 0, value='USBLC6-2SC6', refnum=1)
    s.label(d1.pin('1'), 'DP_J')
    s.label(d1.pin('6'), 'DP')
    s.label(d1.pin('3'), 'DM_J')
    s.label(d1.pin('4'), 'DM')
    s.label(d1.pin('5'), 'VBUS_J')
    s.power(d1.pin('2'), 'GND')
    j = s.place('HC-ST-003-01-J', 'J', 254.0, 180.34, 0, value='USB-A 3.0 receptacle', refnum=1)
    s.label(j.pin('1'), 'VBUS_J')
    s.label(j.pin('2'), 'DM_J')
    s.label(j.pin('3'), 'DP_J')
    s.power(j.pin('4'), 'GND')
    s.label(j.pin('5'), 'SSRX_N')
    s.label(j.pin('6'), 'SSRX_P')
    s.power(j.pin('7'), 'GND')
    s.label(j.pin('8'), 'SSTX_N_J')
    s.label(j.pin('9'), 'SSTX_P_J')
    s.label(j.pin('10'), 'SHIELD')
    s.label(j.pin('11'), 'SHIELD')
    vR(s, 299.72, 180.34, '1M', 'net:SHIELD', 'pwr:GND')
    vC(s, 312.42, 180.34, '1nF 2kV', 'net:SHIELD', 'pwr:GND', size='1206')
    heading(s, 240, 55, 'Net-class directives for the sheet-local nets')
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
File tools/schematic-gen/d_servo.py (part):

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         "UART index ↔ physical port index is fixed by copper (software contract). 8 MHz ±0.4‰ crystal with 33 pF (20 pF CL), 100 nF on every VCC pin, TEST = GND.\n"
         "TNOW: a 4.7 k pull-down on each DTRx/TNOWx pin at power-up selects the TNOW function (CH344Q) and keeps the line low = receive when idle (ROBOTIS TX_Enable idle).\n"
         "RXD pull-ups live on the servo-port sheet next to the receivers (one 10 k per port; RXD3 has no internal pull-up). RESET: 10 k up + 100 nF, test point.\n"
         "ACT (USB configured, active low) drives the green LED. Unused modem / GPIO pins left open (RTS0 and RTS3 must NOT be pulled down: they change pin functions).\n"
         "Open items: V1 (TNOW polarity — scope the dongle), V2 (TNOW release latency vs Return Delay Time). Test points on every TXD / RXD / TNOW.")
    y = 71.12
    for name, shape, nc in HIER_UART:
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        elif n.startswith('TNOW'):
            s.label(p, f'UART{n[4]}_TNOW')
        elif n == 'UD+':
            s.label(p, 'UDP')
        elif n == 'UD-':
            s.label(p, 'UDM')
        elif n in ('XI', 'XO'):
            s.label(p, n)
        elif n == 'RESET':
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        elif n == 'TEST':
            s.power(p, 'GND')
        elif n == 'ACT':
            s.label(p, 'ACT')
        elif p.type != 'no_connect':
            s.nc(p)
    heading(s, 85, 175, 'Crystal, reset, TNOW strap pull-downs, ACT LED')
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    r = vR(s, 220.98, 185.42, '1k', 'pwr:+3V3', None)
    d = s.place('LED_0805_Green', 'D', 220.98, 203.2, 0, value='LED ACT', refnum=1)
    s.connect(top_bottom(r)[1], d.pin('2'))
    s.label(d.pin('1'), 'ACT')
    heading(s, 250, 55, 'USB 2.0 ESD (hub DS4 ↔ CH344 UD+/UD-)')
    d1 = s.place('USBLC6-2SC6_C2687116', 'D', 266.7, 76.2, 0, value='USBLC6-2SC6', refnum=2)
    s.label(d1.pin('6'), 'DS4_DP')
    s.label(d1.pin('1'), 'UDP')
    s.label(d1.pin('4'), 'DS4_DM')
    s.label(d1.pin('3'), 'UDM')
    s.power(d1.pin('5'), '+3V3')
    s.power(d1.pin('2'), 'GND')
    classed(s, 'UDP', 'USB2_HS', 254.0, 96.52)
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         "SN74LVC2G241 (2A = TXD → 2Y = DATA, 2OE = TNOW, 1A = DATA → 1Y = RXD, 1OE# = TNOW only when TTL is selected). Both receivers are off while TNOW is high → no echo in either mode.\n"
         "Mode select JP1 (D2): centre = TNOW, 1-2 bridged (default) = RS-485 receiver enabled, 2-3 = TTL receiver enabled; the unselected enable is pulled high (100 k, weak against the 4.7 k TNOW pull-down).\n"
         "RXD: 10 k pull-up (both receiver outputs wire-OR onto RXD; only one is ever enabled). DATA: 10 k pull-up to +3V3, 22 Ω series, SMF5.0A. A/B: PSM712 array, 120 Ω termination as DNP option.\n"
         "Port power: +12V_SERVO → TPS16630 (ILIM 4.02 k = 4.5 A, dVdT 100 nF, UVLO 8.9 V / OVP 16.8 V, MODE jumper bridged = auto-retry, open = latch; SHDN pulled up, test point for a GPIO e-stop, D3)\n"
         "→ 470 µF/25 V polymer + 100 nF + SMBJ13A → J1 (B4B-EH-A: 1 GND, 2 VDD, 3 D+ = A, 4 D- = B).  +5V_SERVO → TPS25961 (ILIM 27 k ≈ 2 A, OVLO = GND fixed) → 470 µF/10 V + 100 nF + SMBJ6.0A → J2 (B3B-EH-A: 1 GND, 2 VDD, 3 DATA).\n"
         "Net names the project patterns key on: A, B (RS485), DATA (TTL_DATA), VDD_485 / VDD_TTL (PWR_SERVO). Per-instance differences are impossible (values and DNP are shared). Open items: D1, D2, D3, V1.")
    y = 71.12
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    heading(s, 60, 55, 'Front-end: RS-485 transceiver and TTL half-duplex buffer, mode select')
    u1 = s.place('SP3485EN', 'U', 114.3, 88.9, 0, refnum=1, fields={'max_mA': 35})
    s.label(u1.pin('RO'), 'RXD')
    s.label(u1.pin('RE#'), 'RE_485')
    s.label(u1.pin('DE'), 'TNOW')
    s.label(u1.pin('DI'), 'TXD')
    s.power(u1.pin('VCC'), '+3V3')
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    s.label(u1.pin('A'), 'A')
    s.power(u1.pin('GND'), 'GND')
    u2 = s.place('SN74LVC2G241DCU', 'U', 114.3, 127, 0, refnum=2, fields={'max_mA': 5})
    s.label(u2.pin('~{1OE}'), 'OE_TTL')
    s.label(u2.pin('1A'), 'DATA_BUF')
    s.label(u2.pin('2Y'), 'DATA_BUF')
    s.power(u2.pin('GND'), 'GND')
    s.power(u2.pin('VCC'), '+3V3')
    s.label(u2.pin('2OE'), 'TNOW')
    s.label(u2.pin('1Y'), 'RXD')
    s.label(u2.pin('2A'), 'TXD')
    jp = s.place('SolderJumper_3_Bridged12', 'JP', 63.5, 111.76, 0, value='MODE: 1-2 RS-485 (default), 2-3 TTL', nobom=True, lcsc='n/a', refnum=1)
    s.label(jp.pin('A'), 'RE_485')
    s.label(jp.pin('C'), 'TNOW')
    s.label(jp.pin('B'), 'OE_TTL')
    vR(s, 48.26, 139.7, '100k', 'pwr:+3V3', 'net:RE_485')
    vR(s, 78.74, 139.7, '100k', 'pwr:+3V3', 'net:OE_TTL')
    vR(s, 63.5, 139.7, '10k', 'pwr:+3V3', 'net:RXD')
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    u3 = s.place('TPS16630PWPR', 'U', 114.3, 203.2, 0, refnum=3)
    s.chain_pwr(u3.pins_named('IN'), '+12V_SERVO')
    s.power(u3.pin('P_IN'), '+12V_SERVO')
    s.label(u3.pin('UVLO'), 'UVLO_485')
    s.label(u3.pin('OVP'), 'OVP_485')
    s.power(u3.pin('GND'), 'GND')
    s.label(u3.pin('dVdT'), 'DVDT_485')
    s.label(u3.pin('ILIM'), 'ILIM_485')
    s.label(u3.pin('MODE'), 'MODE_485')
    s.label(u3.pin('~{SHDN}'), 'SHDN_485')
    s.nc(u3.pin('IMON'), u3.pin('~{FLT}'), u3.pin('PGOOD'))
    s.chain(*u3.pins_named('OUT'), net='VDD_485')
    s.power(u3.pin('EP'), 'GND')
    vR(s, 33.02, 193.04, '249k', 'pwr:+12V_SERVO', 'net:OVP_485')
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    vC(s, 48.26, 233.68, '100nF', 'net:DVDT_485', 'pwr:GND')
    vR(s, 63.5, 233.68, '4.02k', 'net:ILIM_485', 'pwr:GND')
    jp2 = s.place('SolderJumper_2_Bridged', 'JP', 83.82, 243.84, 0, value='MODE: bridged = auto-retry, open = latch-off', nobom=True, lcsc='n/a', refnum=2)
    s.label(jp2.pin('A'), 'MODE_485')
    s.power(jp2.pin('B'), 'GND')
    vR(s, 162.56, 193.04, '100k', 'pwr:+12V_SERVO', 'net:SHDN_485')
    testpoint(s, 172.72, 185.42, 'SHDN_485')
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    u4 = s.place('TPS25961DRVR', 'U', 317.5, 203.2, 0, refnum=4)
    s.label(u4.pin('OUT'), 'VDD_TTL')
    s.power(u4.pin('OVLO'), 'GND')
    s.label(u4.pin('ILIM'), 'ILIM_TTL')
    s.power(u4.pin('IN'), '+5V_SERVO')
    s.label(u4.pin('EN/UVLO'), 'EN_TTL')
    for p in u4.pins_named('GND'):
        s.power(p, 'GND')
    vR(s, 287.02, 233.68, '27k', 'net:ILIM_TTL', 'pwr:GND')
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
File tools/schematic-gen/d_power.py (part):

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    heading(s, 20, 45, 'Adapter input, fuse, ideal diode')
    # J201 adapter input (rot 90 -> + and - exit to the left)
    j1 = s.place('XT30PW-M', 'J', 40.64, 76.2, 90, refnum=1)
    s.label(j1.pin('+'), 'VIN_RAW')
    s.power(j1.pin('-'), 'GND')
    s.power(j1.pin('3'), 'GND')
    s.power(j1.pin('4'), 'GND')
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    # PWR_FLAG on the fused input (the adapter is the source)
    s.flag((76.2, 50.8))
    s.wire((76.2, 50.8), (76.2, 53.34))
    s.label_xy('VIN_F', 76.2, 53.34, 270)
    # D201 SMBJ24A clamp
    vdiode(s, 'TVS_SMB', 76.2, 96.52, 'net:VIN_F', 'pwr:GND', value='SMBJ24A', lcsc=TVS_SMB['SMBJ24A'], refnum=1)
    # U201 LM74700-Q1
    u = s.place('LM74700QDBVRQ1', 'U', 114.3, 76.2, 0, refnum=1)
    s.label(u.pin('VCAP'), 'VCAP')
    s.power(u.pin('GND'), 'GND')
    s.label(u.pin('EN'), 'VIN_F')
    s.label(u.pin('ANODE'), 'VIN_F')
    s.label(u.pin('GATE'), 'GATE')
    s.power(u.pin('CATHODE'), '+19V_IN')
    vC(s, 91.44, 96.52, '100nF', 'net:VCAP', 'net:VIN_F', refnum=1)
    # Q201 ideal-diode FET: source = VIN_F (anode side), drain = +19V_IN (cathode side)
    q = s.place('CSD18532Q5B', 'Q', 152.4, 76.2, 0, refnum=1)
    s.chain(*q.pins_named('S'), net='VIN_F')
    s.label(q.pin('G'), 'GATE')
    s.chain_pwr(q.pins_named('D') + [q.pin('EP')], '+19V_IN')
    # +19V_IN bulk + flag + bring-up
    heading(s, 175, 45, '+19V_IN bulk, flag, bring-up')
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    # ---------------- controller
    heading(s, 100, 55, 'LM5145 controller')
    u = s.place('LM5145RGYR', 'U', 127, 101.6, 0, refnum=1)
    s.label(u.pin('EN/UVLO'), 'UVLO')
    s.label(u.pin('RT'), 'RT')
    s.label(u.pin('SS/TRK'), 'SS')
    s.label(u.pin('COMP'), 'COMP')
    s.label(u.pin('FB'), 'FB')
    s.power(u.pin('AGND'), 'GND')
    s.nc(u.pin('SYNCOUT'))
    s.label(u.pin('SYNCIN'), 'SYNCIN')
    s.label(u.pin('PGOOD'), 'PGOOD')
    s.label(u.pin('ILIM'), 'ILIM')
    s.power(u.pin('PGND'), 'GND')
    s.label(u.pin('LO'), 'LO')
    s.label(u.pin('VCC'), 'VCC')
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    testpoint(s, 220.98, 160.02, 'PGOOD')
    jp = s.place('SolderJumper_3_Bridged12', 'JP', 220.98, 190.5, 0, value='SYNCIN: 1-2 GND=DEM, 2-3 VCC=FPWM', nobom=True, lcsc='n/a', refnum=1)
    s.power(jp.pin('A'), 'GND')
    s.label(jp.pin('C'), 'SYNCIN')
    s.label(jp.pin('B'), 'VCC')
    # ---------------- power stage
    heading(s, 250, 55, 'Power stage: Q1 high side, Q2 low side, inductor, output bank')
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    s.label(u.pin('RT/CLK'), 'RT')
    s.label(u.pin('SW'), 'SW')
    s.power(u.pin('GND'), 'GND')
    s.label(u.pin('COMP'), 'COMP')
    s.label(u.pin('FB'), 'FB')
    s.power(u.pin('EP'), 'GND')
    vR(s, 30.48, 129.54, '442k', 'pwr:+19V_IN', 'net:EN')
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    u2 = s.place('TLV62569DBVR', 'U', 292.1, 88.9, 0, refnum=2)
    s.power(u2.pin('EN'), '+5V_USB')
    s.power(u2.pin('GND'), 'GND')
    s.label(u2.pin('SW'), 'SW_3V3')
    s.power(u2.pin('VIN'), '+5V_USB')
    s.label(u2.pin('FB'), 'FB_3V3')
    L2 = s.place('SMNR4020-2.2UH', 'L', 330.2, 101.6, 0, value='2.2uH 3.4A', refnum=2)
    s.label(L2.pin('1'), 'SW_3V3')
    s.power(L2.pin('2'), '+3V3')
    vR(s, 355.6, 129.54, '453k', 'pwr:+3V3', 'net:FB_3V3')
    vC(s, 368.3, 129.54, '6.8pF', 'pwr:+3V3', 'net:FB_3V3')
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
